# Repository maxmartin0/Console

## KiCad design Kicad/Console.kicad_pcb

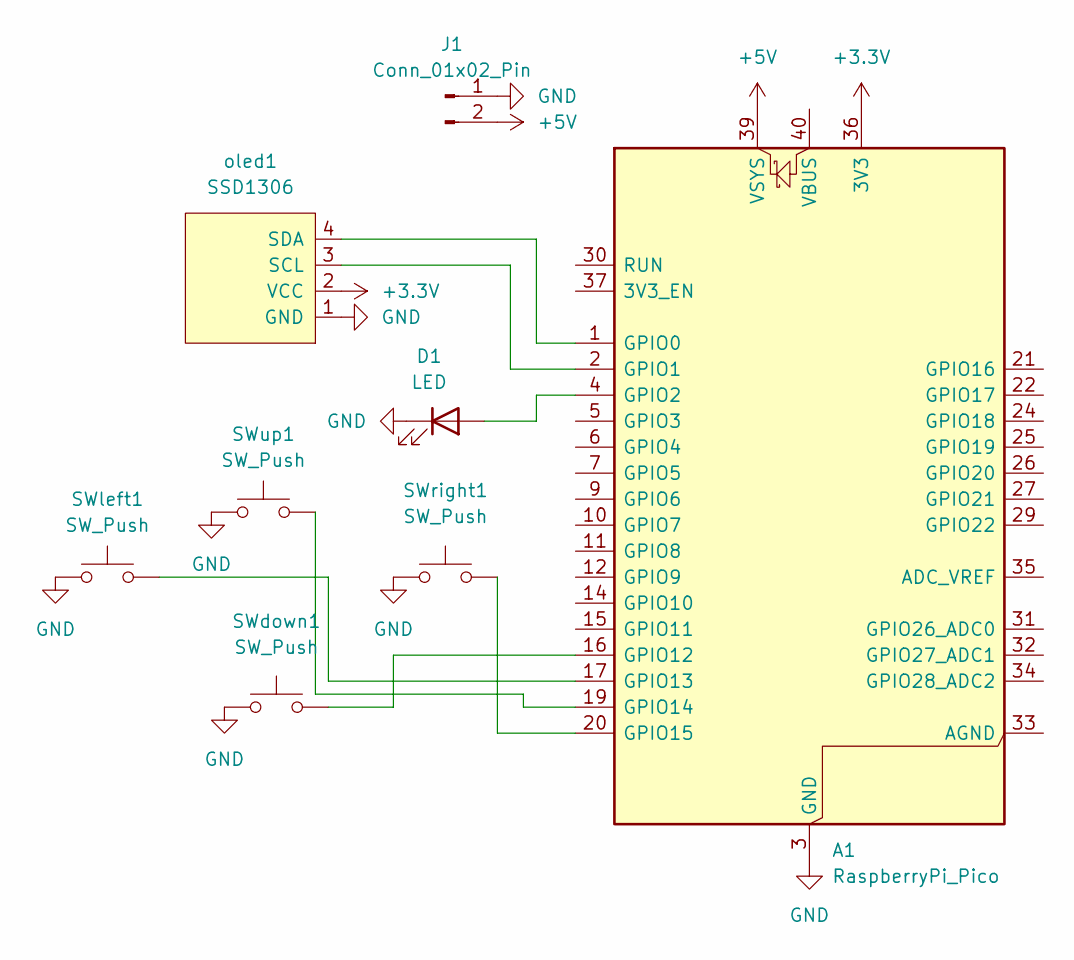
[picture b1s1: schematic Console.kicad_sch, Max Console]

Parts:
A1: RaspberryPi_Pico; RaspberryPi_Pico_Common_SMD
D1: LED; LED_D5.0mm_Horizontal_O1.27mm_Z3.0mm_Clear
J1: Conn_01x02_Pin; PinHeader_1x02_P2.54mm_Vertical
SWdown1: SW_Push; SW_Push_1P1T_NO_E-Switch_TL3301NxxxxxG
SWleft1: SW_Push; SW_Push_1P1T_NO_E-Switch_TL3301NxxxxxG
SWright1: SW_Push; SW_Push_1P1T_NO_E-Switch_TL3301NxxxxxG
SWup1: SW_Push; SW_Push_1P1T_NO_E-Switch_TL3301NxxxxxG
oled1: SSD1306; 128x64OLED

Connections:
+3.3V: A1.36 (3V3), oled1.2 (VCC)
+5V: A1.39 (VSYS), J1.2
GND: A1.3 (GND), A1.8 (GND), A1.13 (GND), A1.18 (GND), A1.23 (GND), A1.28 (GND), A1.38 (GND), D1.1 (K), J1.1, SWdown1.1, SWleft1.1, SWright1.1, SWup1.1, oled1.1 (GND)
unnamed: A1.1 (GPIO0), oled1.4 (SDA)
unnamed: A1.2 (GPIO1), oled1.3 (SCL)
unnamed: A1.4 (GPIO2), D1.2 (A)
unnamed: A1.16 (GPIO12), SWdown1.2
unnamed: A1.17 (GPIO13), SWleft1.2
unnamed: A1.19 (GPIO14), SWup1.2
unnamed: A1.20 (GPIO15), SWright1.2

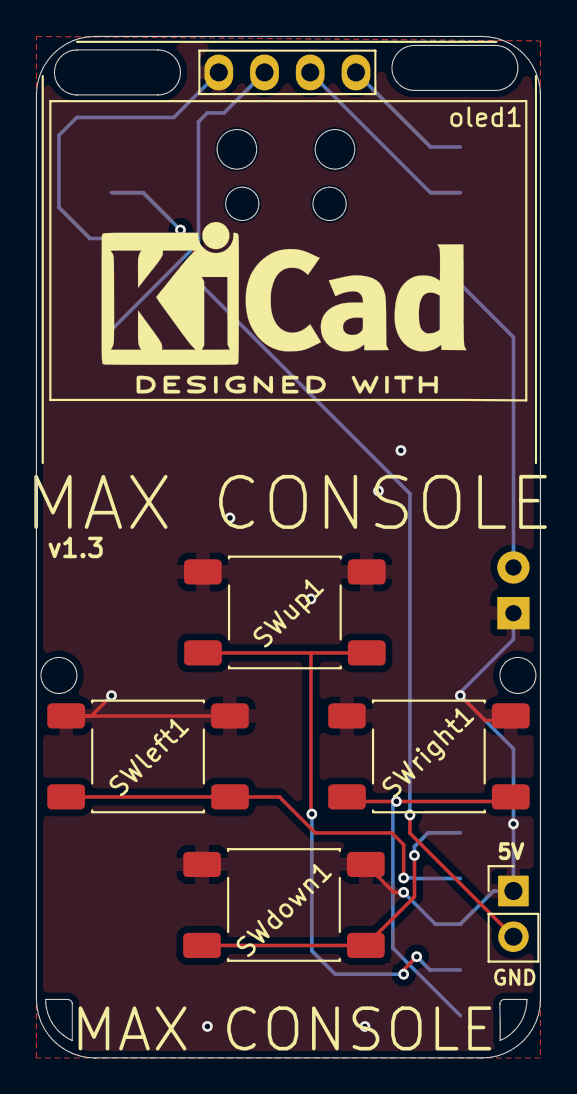
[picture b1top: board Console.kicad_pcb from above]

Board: 2 copper layers, 28.0 x 56.8 mm, 8 parts (1 on the bottom side), 10 nets.
